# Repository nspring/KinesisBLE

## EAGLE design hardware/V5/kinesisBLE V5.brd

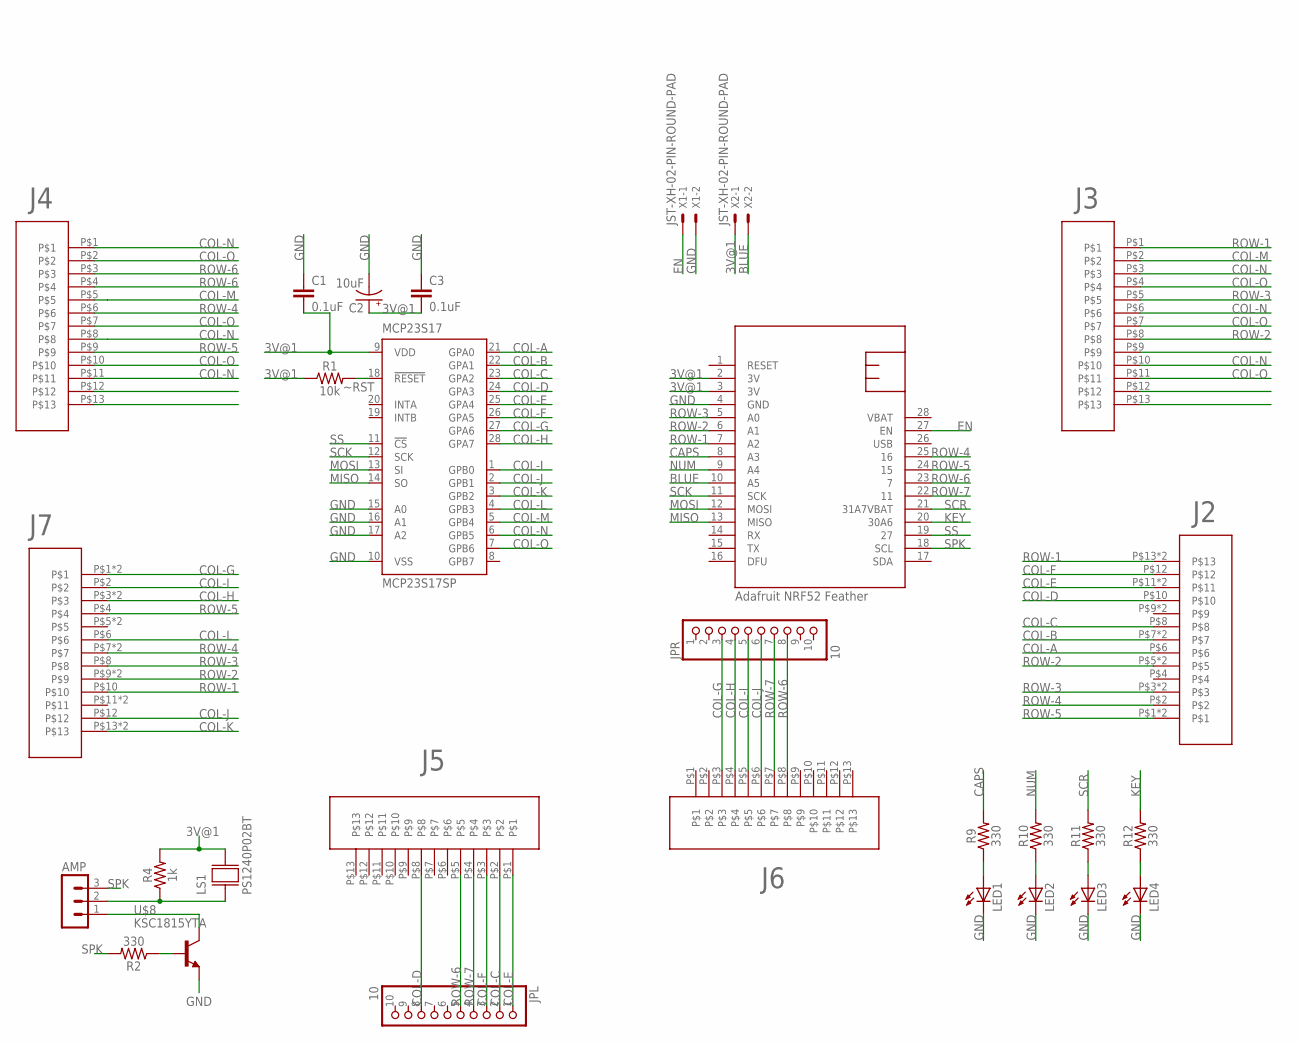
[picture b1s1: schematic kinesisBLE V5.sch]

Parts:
AMP: MA03-1
C1, C3: 0.1uF; CAP-PTH-SMALL-KIT
C2: 10uF; CPOL-RADIAL-2.5MM-5MM
JPL: 10; 1X10
JPR: 10; 1X10
LED1, LED2, LED3, LED4: LED3MM
LS1: PS1240P02BT; XDCR_PS1240P02BT
MCP23S17: MCP23S17SP; DIL28-3
R1: 10k; AXIAL-0.3
R2, R9, R10, R11, R12: 330; AXIAL-0.3
R4: 1k; AXIAL-0.3
U$1: NRF52FEATHER
U$2, U$3, U$6, U$7: TOPLINKS_STAPELBERG
U$4, U$5: MOLEX-39-53-215X-DEVMOLEX-39-53-215X-DEV; MOLEX-39-53-215X-PKG
U$8: KSC1815YTA; TO92-ECB
X1, X2: JST-XH-02-PIN-ROUND-PAD; JST-XH-02-PACKAGE-ROUND-PAD

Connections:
3V@1: C1.2, C2.1 (+), C3.2, LS1.2, MCP23S17.9 (VDD), R1.P$1 (1), R4.P$2 (2), U$1.2 (3V), U$1.3 (3V), X2.1
BLUE: U$1.10 (A5), X2.2
CAPS: R9.P$2 (2), U$1.8 (A3)
COL-A: MCP23S17.21 (GPA0), U$5.P$6
COL-B: MCP23S17.22 (GPA1), U$5.P$7, U$5.P$7@2
COL-C: JPL.2, MCP23S17.23 (GPA2), U$5.P$8, U$6.P$2
COL-D: JPL.8, MCP23S17.24 (GPA3), U$5.P$10, U$6.P$8
COL-E: JPL.1, MCP23S17.25 (GPA4), U$5.P$11, U$5.P$11@2, U$6.P$1
COL-F: JPL.3, MCP23S17.26 (GPA5), U$5.P$12, U$6.P$3
COL-G: JPR.3, MCP23S17.27 (GPA6), U$4.P$1, U$4.P$1@2, U$7.P$3
COL-H: JPR.4, MCP23S17.28 (GPA7), U$4.P$3, U$4.P$3@2, U$7.P$4
COL-I: JPR.5, MCP23S17.1 (GPB0), U$4.P$2, U$7.P$5
COL-J: JPR.6, MCP23S17.2 (GPB1), U$4.P$12, U$7.P$6
COL-K: MCP23S17.3 (GPB2), U$4.P$13, U$4.P$13@2
COL-L: MCP23S17.4 (GPB3), U$4.P$6
COL-M: MCP23S17.5 (GPB4), U$2.P$5, U$3.P$2
COL-N: MCP23S17.6 (GPB5), U$2.P$1, U$2.P$8, U$2.P$11, U$3.P$3, U$3.P$6, U$3.P$10
COL-O: MCP23S17.7 (GPB6), U$2.P$2, U$2.P$7, U$2.P$10, U$3.P$4, U$3.P$7, U$3.P$11
EN: U$1.27 (EN), X1.1
GND: C1.1, C2.2 (-), C3.1, LED1.K (C), LED2.K (C), LED3.K (C), LED4.K (C), MCP23S17.10 (VSS), MCP23S17.15 (A0), MCP23S17.16 (A1), MCP23S17.17 (A2), U$1.4 (GND), U$8.E, X1.2
KEY: R12.P$2 (2), U$1.20 (30A6)
MISO: MCP23S17.14 (SO), U$1.13 (MISO)
MOSI: MCP23S17.13 (SI), U$1.12 (MOSI)
unnamed: LED1.A, R9.P$1 (1)
unnamed: AMP.1, U$8.C
unnamed: AMP.2, LS1.1, R4.P$1 (1)
unnamed: R2.P$1 (1), U$8.B
unnamed: LED2.A, R10.P$1 (1)
unnamed: LED3.A, R11.P$1 (1)
unnamed: LED4.A, R12.P$1 (1)
NUM: R10.P$2 (2), U$1.9 (A4)
ROW-1: U$1.7 (A2), U$3.P$1, U$4.P$10, U$5.P$13, U$5.P$13@2
ROW-2: U$1.6 (A1), U$3.P$8, U$4.P$9, U$4.P$9@2, U$5.P$5, U$5.P$5@2
ROW-3: U$1.5 (A0), U$3.P$5, U$4.P$8, U$5.P$3, U$5.P$3@2
ROW-4: U$1.25 (16), U$2.P$6, U$4.P$7, U$4.P$7@2, U$5.P$2
ROW-5: U$1.24 (15), U$2.P$9, U$4.P$4, U$5.P$1, U$5.P$1@2
ROW-6: JPL.5, JPR.8, U$1.23 (7), U$2.P$3, U$2.P$4, U$6.P$5, U$7.P$8
ROW-7: JPL.4, JPR.7, U$1.22 (11), U$6.P$4, U$7.P$7
SCK: MCP23S17.12 (SCK), U$1.11 (SCK)
SCR: R11.P$2 (2), U$1.21 (31A7VBAT)
SPK: AMP.3, R2.P$2 (2), U$1.18 (SCL)
SS: MCP23S17.11 (!CS), U$1.19 (27)
VBAT: U$1.28 (VBAT)
~RST: MCP23S17.18 (!RESET), R1.P$2 (2)

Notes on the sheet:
Adafruit NRF52 Feather

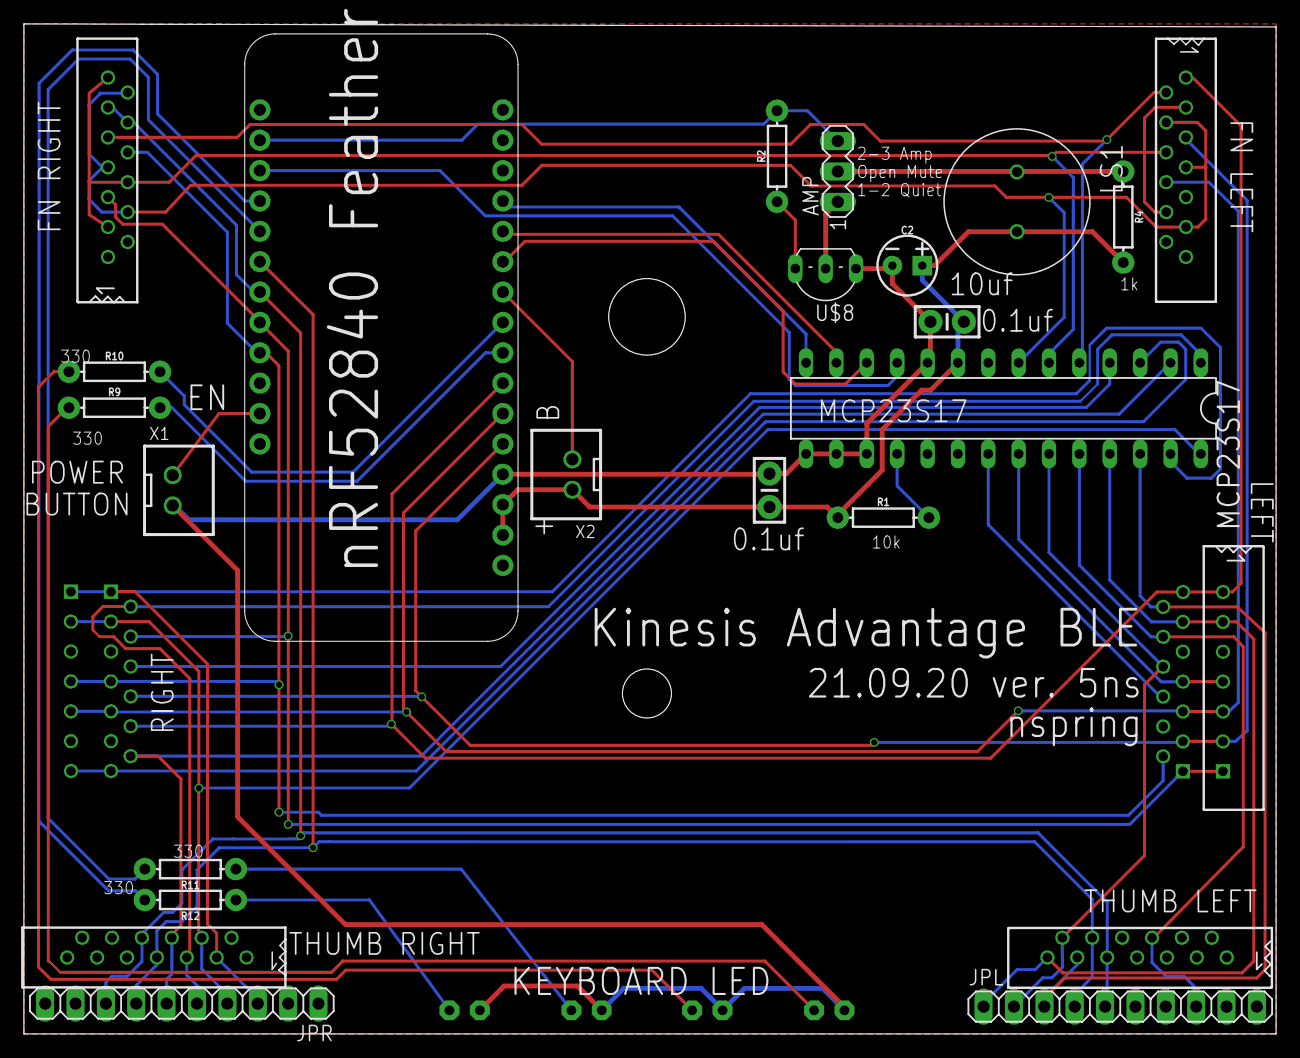
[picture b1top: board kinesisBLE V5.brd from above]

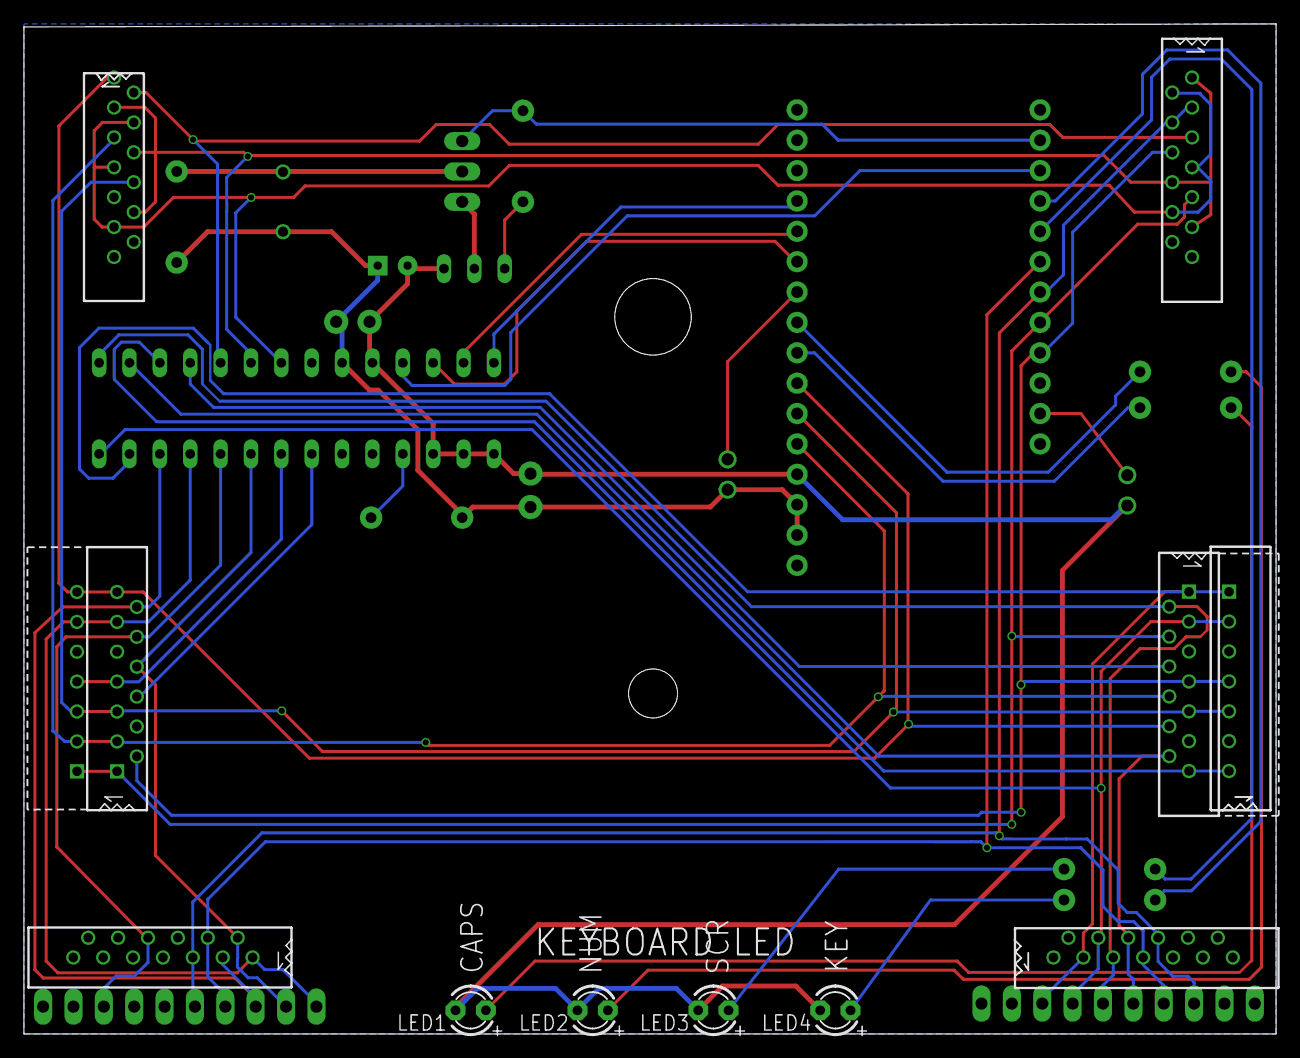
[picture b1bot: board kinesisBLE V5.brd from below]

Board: 2 copper layers, 104.7 x 84.5 mm, 29 parts (6 on the bottom side), 43 nets.

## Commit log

2020-09-14 work in progress
2020-09-15 first cut routing
2020-09-15 minor reroute, ERC fixes
2020-09-15 updates to power trace width, spacing
2020-09-15 replace ground planes
2020-09-16 increase / standardize trace widths
2020-09-17 buzzer draft
2020-09-17 touches
2020-09-25 submit

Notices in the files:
parts and their libraries:
SparkFun-Resistors: Licensing: Creative Commons ShareAlike 4.0 International - https://creativecommons.org/licenses/by-sa/4.0
